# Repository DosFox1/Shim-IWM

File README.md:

# What is the Shim IWM?

A simple electronic "shim" to replace an Integrated Woz Machine (the apple floppy controller) in a Macintosh. It contains just enough hardware to pass the initial boot check, and boot into Mac OS via SCSI. This board is also referred to as the "SCHWIM", as I cannot say no to a bad pun.
This setup has been tested on a Macintosh Plus, Macintosh SE FDHD (which expects a SWIM), as well as a Macintosh LC ii. It is likely this will work in any Macintosh that requires an IWM or SWIM.

If you need to repair a Macintosh that has a bad IWM, but you are okay with losing Floppy support - then this is the board for you!

Many thanks to Matt Evans (https://github.com/evansm7) for providing help with this project - specifically the data to be put on the databus, and initially testing the modification that led to this board in QEMU as well as Pico-mac.
Many thanks to Max1zzz (https://github.com/max234252) for testing the SCHWIM in an SE FDHD, as well as in a Macintosh LC ii. 

# What this is not

This is in no way a full replacement for the IWM. This is only meant to get the system to get past checking for the floppy controller, and then to boot from a different boot medium - such as ROM, SCSI or IDE. 
It will **NOT:**
1) give you full floppy support
2) work in an Apple ii
3) give you HD20 emulation support
4) force you to eat toast
5) gain sentience and try to take over the world (probably)

# How does this even work? 

First of all, I want to say that I HATE THAT THIS SOLUTION WORKS. 
It is so so so dumb and backwards. If you check internal Apple documents of the era, you will literally find references to engineers saying they don't want to touch the IWM or the associated driver. 

https://bitsavers.org/pdf/apple/mac/prototypes/1985_YACC/YACC_Description.pdf
http://bitsavers.informatik.uni-stuttgart.de/pdf/apple/mac/prototypes/1985_Big_Mac/BIGMAC_Bringup.pdf

Safe to say the IWM and the associated driver are a bit of a headache. 
So how does this all work??

Effectively, the circuitry works by using an OR gate to monitor the state of Address 0 (also referred to as A1 in some schematics, it's also an enable pin - just to annoy you - basically it's pin 3), as well as the /DEV pin (the enable pin for the IWM itself - Pin 10). When both are low (active low pins), they enable the 74LS244 octal buffer to put the data 0xDF (1101111 - D7->D0) onto the data bus, which has been pulled high and low via eight 4.7K resistors. 

On boot, the Macintosh checks for the presence of the IWM by reading the Status register. 
The status register contains a single byte of data, with each bit representing the status of a setting in the IWM. These are as follows: 

<pre>
0 - Latch mode (set in async mode, 1 = async mode) - Macintosh is async, so set to 1
1 - synchronous handshake protocol (1 = async mode) - Macintosh is async, so set to 1 again
2 - 1 second onboard timer enable (1 = disabled, 0 = keep motor on for 1 second) - timer disabled, set to 1
3 - slow mode/fast mode (bit cell time - 1 = 2us, 0 = 4us) - bit sel is 2us in a Macintosh 
4 - clock - 7mhz/8mhz (clcok input, 1 - 8mhz, 0 = 7mhz) - Macintosh clock is 8mhz, set to 1
5 - /ENBL1 or /ENBL2 is currently active (0 = active, 1 = inactive) - IWM is enabled, set to 0
6 - MZ (reserved for future compatability - should be read as 0, but 1 apparently works) - set to 1, could be 0?
7 - Sense input (1 = sense is high, 0 = sense is low. Could be either, but 1 works) - set to 1, but could be 0?
</pre>

So from  D7 to D0, the data should read:
<pre>
0 - 1
1 - 1
2 - 1
3 - 1
4 - 1
5 - 0
6 - 1
7 - 1
</pre>

Which in turn, represented in hex, is 0xDF, or 1101111 in binary.

Once the status register is read, the mode register is read straight after. D0 to D4 are the same as the mode register. The mode register contains: 

<pre>
0 - Latch mode (set in async mode, 1 = async mode) - Macintosh is async, so set to 1
1 - synchronous handshake protocol (1 = async mode) - Macintosh is async, so set to 1 again
2 - 1 second onboard timer enable (1 = disabled, 0 = keep motor on for 1 second) - timer disabled, set to 1
3 - slow mode/fast mode (bit cell time - 1 = 2us, 0 = 4us) - bit sel is 2us in a Macintosh 
4 - clock - 7mhz/8mhz (clcok input, 1 - 8mhz, 0 = 7mhz) - Macintosh clock is 8mhz, set to 1
5 - test mode (1 = test mode, 0 = normal operation) - set to normal operation - 0
6 - MZ-reset (reserved for future compatability - should be read as 0, but 1 apparently works) - set to 1, could be 0?
7 - Reserved for Future expansion, so could be either, but 1 works - set to 1, but could be 0?
</pre>

So again, seting the data to 1101111 works for the mode register as well. I might be wrong about that explanation, but hey this implementation works!
After all that, the system does not check the IWM again - or at least when it does, it see that the sense line is still high, so it believes that no disk has been inserted. 

It basically just sits there, reading a newspaper saying "keep going, you're all good. No problems here", and the Macintosh effectively goes "sounds good!" and keeps booting. 

It is so mind numblingy simple, I almost hate it!

# Construction

Assembling the board is relatively simple, and can be assembled by anyone with decent soldering abilities. The PCB routing was done in about fifteen minutes on my lunch break, so it is pretty dire. This board is currently at VDEV1,and I'm happy to report that they do work! Please note, to make the best electrical connection from the IWM socket to the SCHWIM - it's ideal to add a turned pin socket between the SCHWIM board and the logic board.

The BOM is as follows, all parts are generic garden variety components:

<pre>
Part     Value          Package          Library       Position (mm)         Orientation

C1       100n 50V       CAP_5.08MM_PITCH Capacitors TH (9.8 6.9)             R180
C2       100n 50V       CAP_5.08MM_PITCH Capacitors TH (16.9 21.7)           R180
R1       4k7            RESISTORTHRUHOLE Resistors TH  (13.5 20.6)           R180
R2       4k7            RESISTORTHRUHOLE Resistors TH  (13.5 24.1)           R180
R3       4k7            RESISTORTHRUHOLE Resistors TH  (13.5 27.6)           R180
R4       4k7            RESISTORTHRUHOLE Resistors TH  (13.5 31.1)           R180
R5       4k7            RESISTORTHRUHOLE Resistors TH  (13.5 34.6)           R180
R6       4k7            RESISTORTHRUHOLE Resistors TH  (32 34.1)             R180
R7       4k7            RESISTORTHRUHOLE Resistors TH  (32 37.1)             R180
R8       4k7            RESISTORTHRUHOLE Resistors TH  (32 31.1)             R180
CN1      IWM            Turn Pin Header  Headers       (20 9.6)              R0
U1       74LS32N        DIL14            74xx-us       (27.88 24.19)         R0
U2       74LS244N       DIL20            74xx-eu       (26.3 9.6)            R0
</pre>

The board should be able to fit over the ROMs in a Macintosh Plus, it may be necessary to add another DIP28 socket between the board and the IWM socket. 

I never got around to designing an SMD version of the SCHWIM - but the wonderful HKZ did!
See here for the SMD version:
https://github.com/hkzlab/schwim_repacked

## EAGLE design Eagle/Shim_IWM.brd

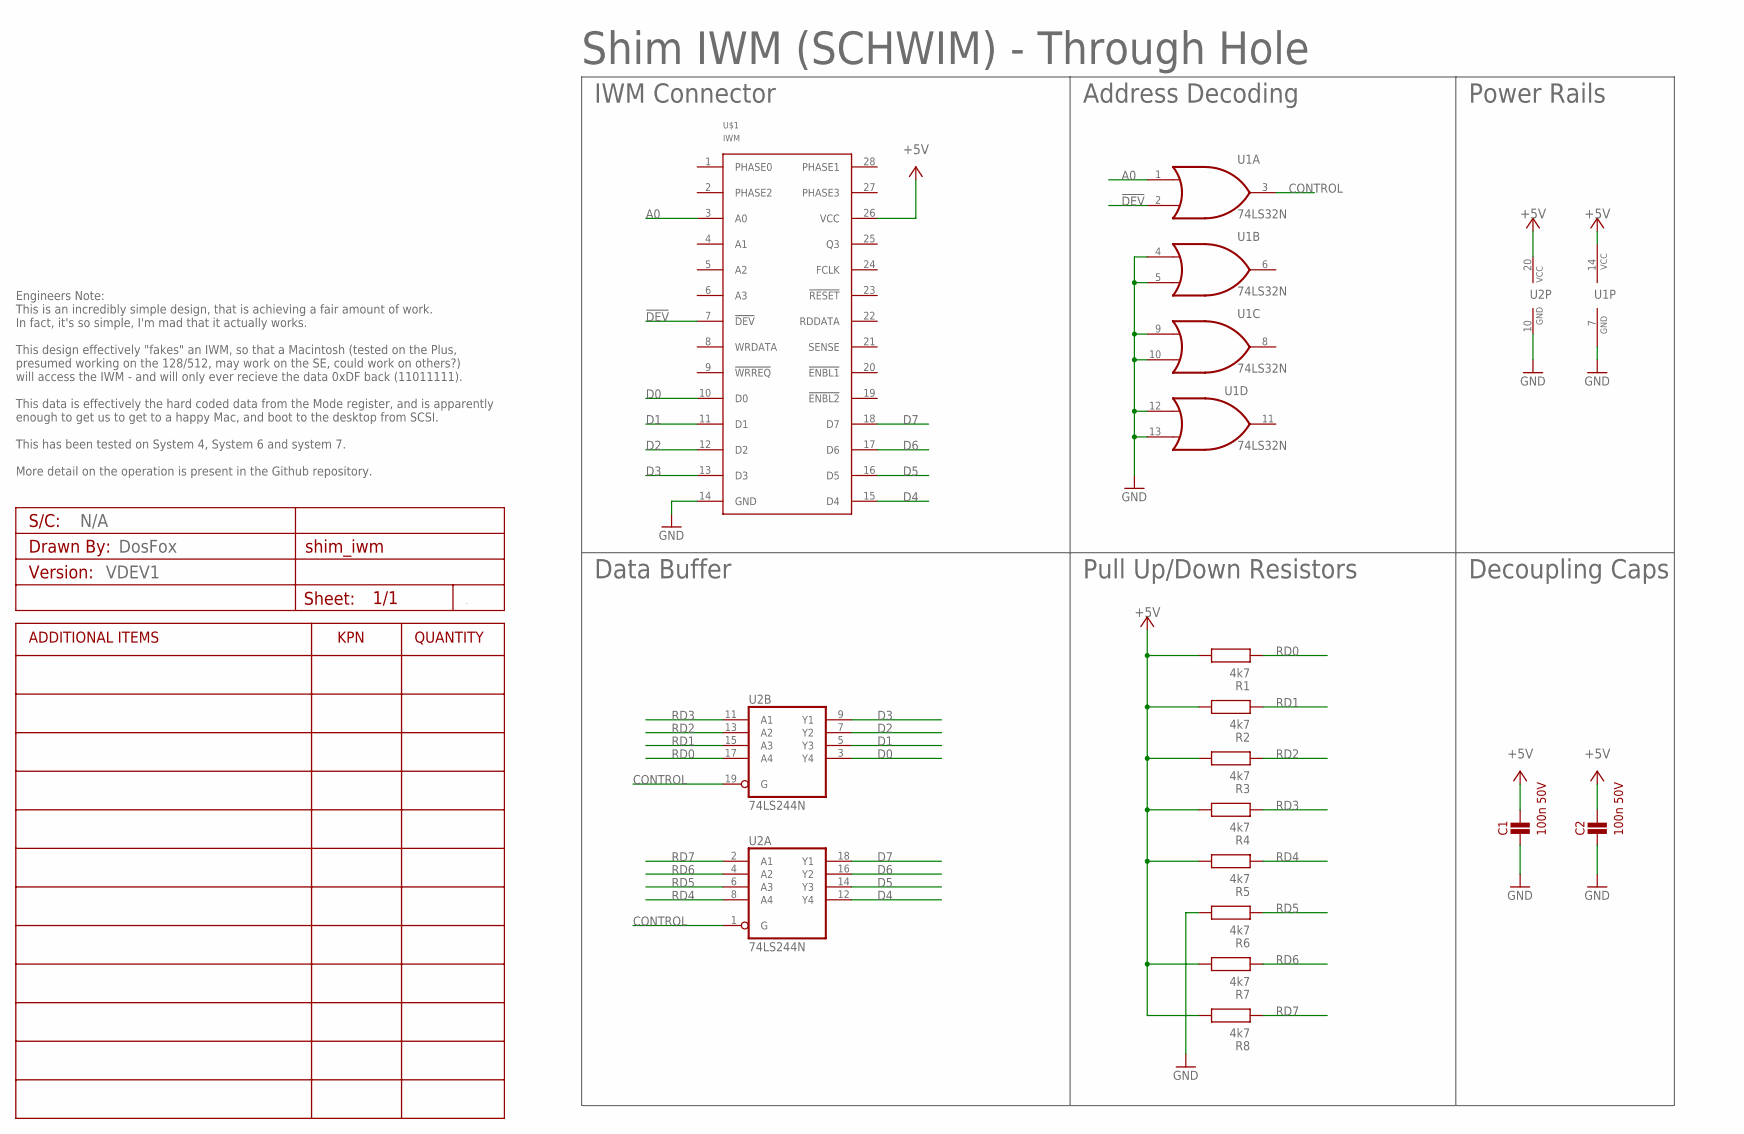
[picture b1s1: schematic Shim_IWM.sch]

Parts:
A1: VDEV1; PCB_CUSTOM_DETAILS
C1, C2: 100n 50V; CAP_5.08MM_PITCH
R1, R2, R3, R4, R5, R6, R7, R8: 4k7; RESISTORTHRUHOLE
U1: 74LS32N; DIL14
U2: 74LS244N; DIL20
U$1: IWM; DIP28

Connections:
!DEV: U1.2 (I1), U$1.7 (!DEV)
+5V: C1.P$2, C2.P$2, R1.P$2, R2.P$2, R3.P$2, R4.P$2, R5.P$2, R7.P$2, R8.P$2, U1.14 (VCC), U2.20 (VCC), U$1.26 (VCC)
A0: U1.1 (I0), U$1.3 (A0)
CONTROL: U1.3 (O), U2.1 (G), U2.19 (G)
D0: U2.3 (Y4), U$1.10 (D0)
D1: U2.5 (Y3), U$1.11 (D1)
D2: U2.7 (Y2), U$1.12 (D2)
D3: U2.9 (Y1), U$1.13 (D3)
D4: U2.12 (Y4), U$1.15 (D4)
D5: U2.14 (Y3), U$1.16 (D5)
D6: U2.16 (Y2), U$1.17 (D6)
D7: U2.18 (Y1), U$1.18 (D7)
GND: C1.P$1, C2.P$1, R6.P$2, U1.4 (I0), U1.5 (I1), U1.7 (GND), U1.9 (I0), U1.10 (I1), U1.12 (I0), U1.13 (I1), U2.10 (GND), U$1.14 (GND)
RD0: R1.P$1, U2.17 (A4)
RD1: R2.P$1, U2.15 (A3)
RD2: R3.P$1, U2.13 (A2)
RD3: R4.P$1, U2.11 (A1)
RD4: R5.P$1, U2.8 (A4)
RD5: R6.P$1, U2.6 (A3)
RD6: R7.P$1, U2.4 (A2)
RD7: R8.P$1, U2.2 (A1)

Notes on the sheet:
Shim IWM (SCHWIM) - Through Hole
IWM Connector
Address Decoding
Power Rails
Decoupling Caps
Pull Up/Down Resistors
Data Buffer
DosFox
N/A
Engineers Note: This is an incredibly simple design, that is achieving a fair amount of work. In fact, it's so simple, I'm mad that it actually works. This design effectively "fakes" an IWM, so that a Macintosh (tested on the Plus, presumed working on the 128/512, may work on the SE, could work on 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

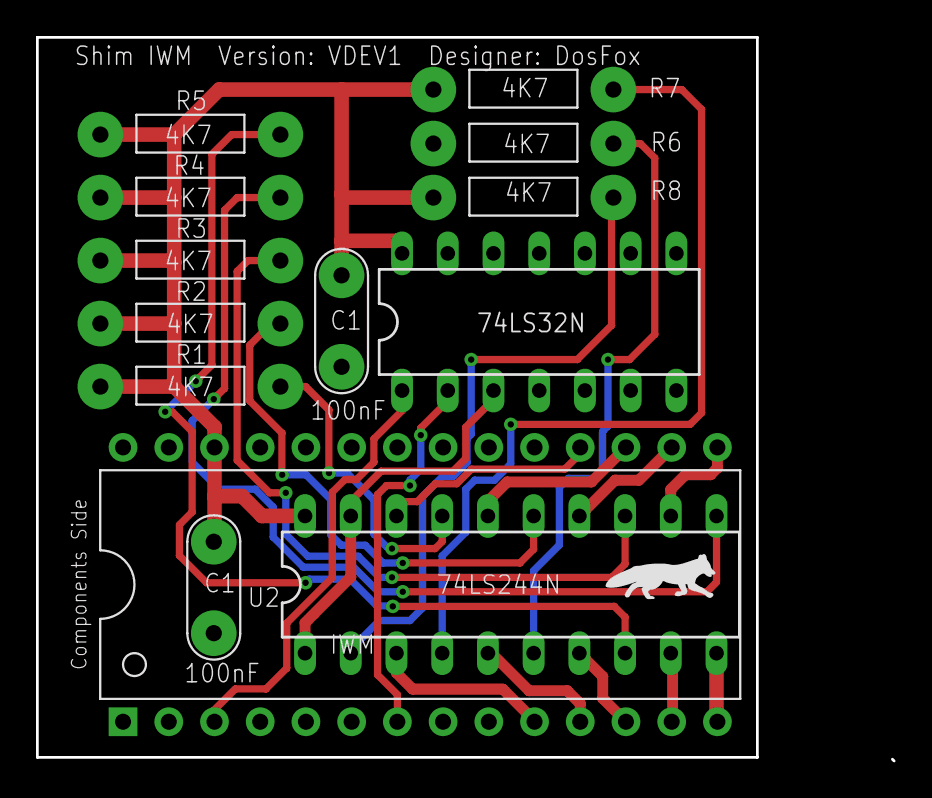
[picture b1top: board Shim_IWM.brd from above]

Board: 2 copper layers, 47.6 x 40.2 mm, 14 parts (0 on the bottom side), 21 nets.

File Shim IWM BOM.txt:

Partlist

Exported from Shim_IWM.brd at 29/Aug/24 13:13

EAGLE Version 9.6.2 Copyright (c) 1988-2020 Autodesk, Inc.

Assembly variant: 

Part     Value          Package          Library       Position (mm)         Orientation

C1       100n 50V       CAP_5.08MM_PITCH Capacitors TH (9.8 6.9)             R180
C2       100n 50V       CAP_5.08MM_PITCH Capacitors TH (16.9 21.7)           R180
R1       4k7            RESISTORTHRUHOLE Resistors TH  (13.5 20.6)           R180
R2       4k7            RESISTORTHRUHOLE Resistors TH  (13.5 24.1)           R180
R3       4k7            RESISTORTHRUHOLE Resistors TH  (13.5 27.6)           R180
R4       4k7            RESISTORTHRUHOLE Resistors TH  (13.5 31.1)           R180
R5       4k7            RESISTORTHRUHOLE Resistors TH  (13.5 34.6)           R180
R6       4k7            RESISTORTHRUHOLE Resistors TH  (32 34.1)             R180
R7       4k7            RESISTORTHRUHOLE Resistors TH  (32 37.1)             R180
R8       4k7            RESISTORTHRUHOLE Resistors TH  (32 31.1)             R180
CN1      IWM            Turn Pin Header  Headers       (20 9.6)              R0
U1       74LS32N        DIL14            74xx-us       (27.88 24.19)         R0
U2       74LS244N       DIL20            74xx-eu       (26.3 9.6)            R0

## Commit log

2024-10-21 Rename Complete SCHWIM Board.jpg to Images/Complete SCHWIM Board.jpg
2024-10-21 Add files via upload
    GITHUB STOP NUKING MY FILES
2024-10-21 Rename Shim IWM Back.png to Images/Shim IWM Back.png
2024-10-21 Rename Shim IWM Front.png to Images/Shim IWM Front.png
2024-10-21 Rename Shim_IWM.brd to Eagle/Shim_IWM.brd
2024-10-21 Rename Shim_IWM.sch to Eagle/Shim_IWM.sch
2024-10-21 Rename Shim_IWM.pdf to Schematic/Shim_IWM.pdf
2024-10-21 Rename Shim_IWM_VDEV1.zip to Gerbers/Shim_IWM_VDEV1.zip
2024-10-21 Create LICENSE
    Added CERN Strongly Reciprocal License
